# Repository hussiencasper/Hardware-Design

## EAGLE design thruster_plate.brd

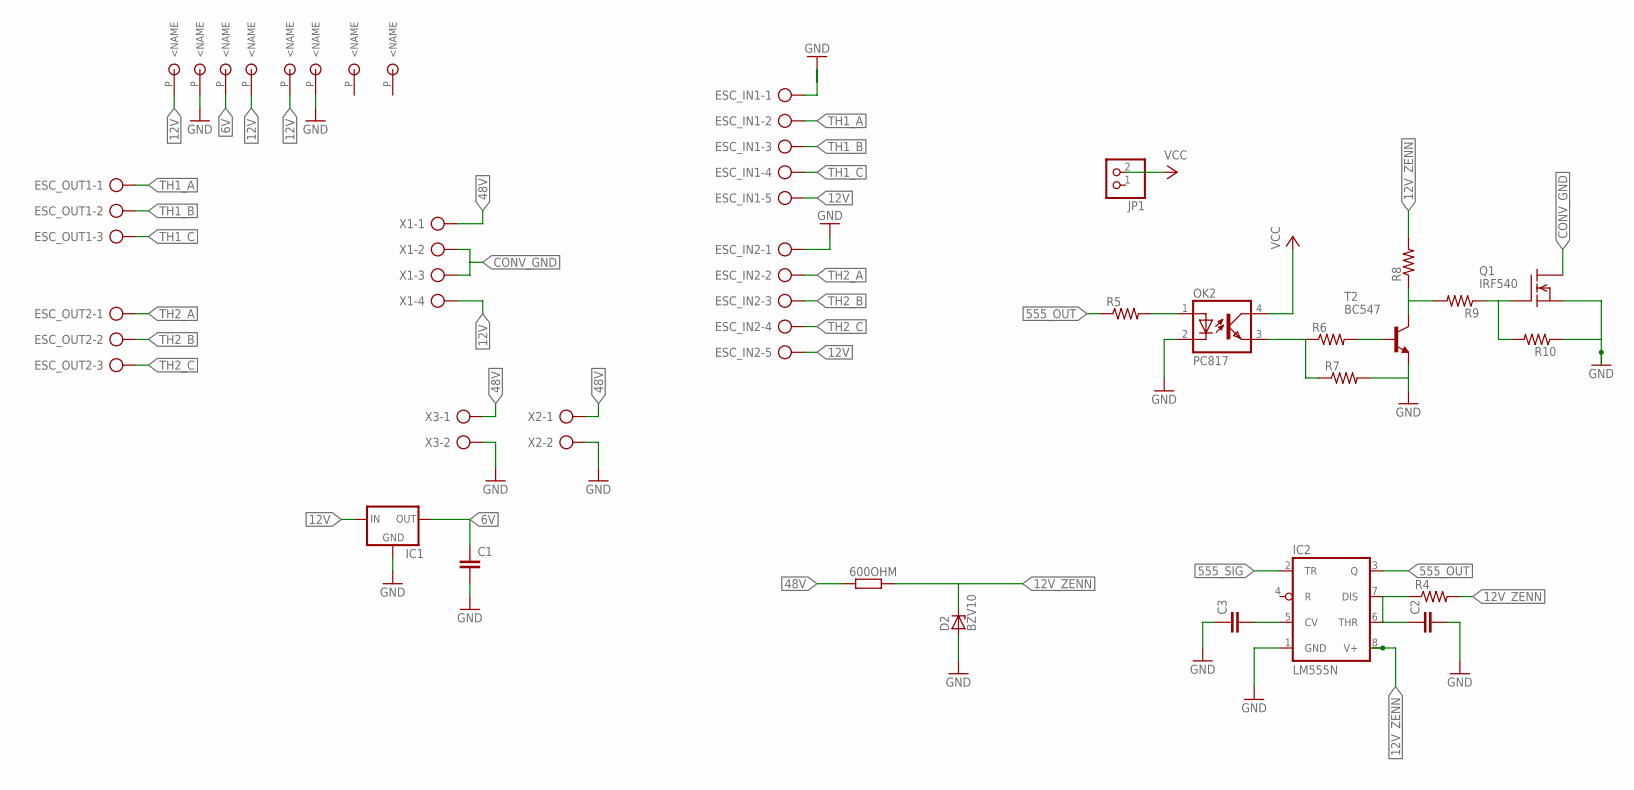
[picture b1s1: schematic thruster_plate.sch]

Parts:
12, 12-1, 12-2, 12-3, 12-4, 12-6: CU-SPACER
600OHM: R-EU_V235/17; V235/17
C1, C3: C-EU050-024X044; C050-024X044
C2: C-EU050-035X075; C050-035X075
D2: BZV10; DO34Z7
ESC_IN1, ESC_IN2: AK500/5
ESC_OUT1, ESC_OUT2: AK500/3
IC1: 78XXL
IC2: LM555N; DIL08
JP1: PINHD-1X2; 1X02
OK2: PC817; DIL04
Q1: IRF540; TO220
R4, R5, R6, R7, R8, R9, R10: R-US_0204/7; 0204/7
T2: BC547; TO92
U$2, U$3: CU-SPACER
X1: AK500/4
X2, X3: AK500/2

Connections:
6V: C1.1, IC1.OUT, U$3.P
12V: 12.P, 12-1.P, 12-2.P, ESC_IN1.5, ESC_IN2.5, IC1.IN, X1.4
12V_ZENN: 600OHM.2, D2.C, IC2.8 (V+), R4.2, R8.2
48V: 600OHM.1, X1.1, X2.1, X3.1
555_OUT: IC2.3 (Q), R5.1
555_SIG: IC2.2 (TR)
CONV_GND: Q1.2 (D), X1.2, X1.3
GND: 12-3.P, C1.2, C2.2, C3.1, D2.A, ESC_IN1.1, ESC_IN2.1, IC1.GND, IC2.1 (GND), OK2.2 (C), Q1.3 (S), R7.2, R10.1, T2.1 (E), U$2.P, X2.2, X3.2
unnamed: OK2.1 (A), R5.2
unnamed: OK2.3 (EMIT), R6.1, R7.1
unnamed: R6.2, T2.2 (B)
unnamed: R8.1, R9.2, T2.3 (C)
unnamed: C3.2, IC2.5 (CV)
unnamed: Q1.1 (G), R9.1, R10.2
unnamed: C2.1, IC2.6 (THR), IC2.7 (DIS), R4.1
TH1_A: ESC_IN1.2, ESC_OUT1.1
TH1_B: ESC_IN1.3, ESC_OUT1.2
TH1_C: ESC_IN1.4, ESC_OUT1.3
TH2_A: ESC_IN2.2, ESC_OUT2.1
TH2_B: ESC_IN2.3, ESC_OUT2.2
TH2_C: ESC_IN2.4, ESC_OUT2.3
VCC: JP1.2, OK2.4 (COL)

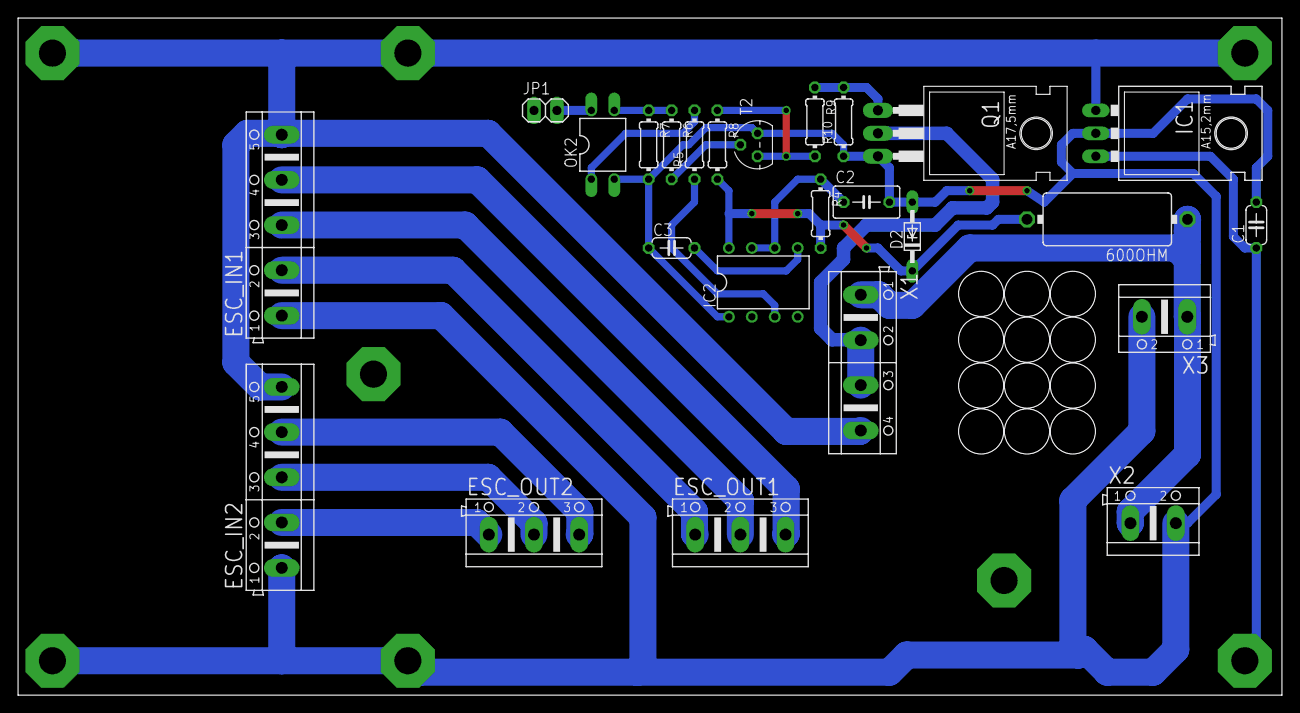
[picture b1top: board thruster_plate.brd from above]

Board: 2 copper layers, 140.0 x 75.0 mm, 33 parts (0 on the bottom side), 21 nets.
